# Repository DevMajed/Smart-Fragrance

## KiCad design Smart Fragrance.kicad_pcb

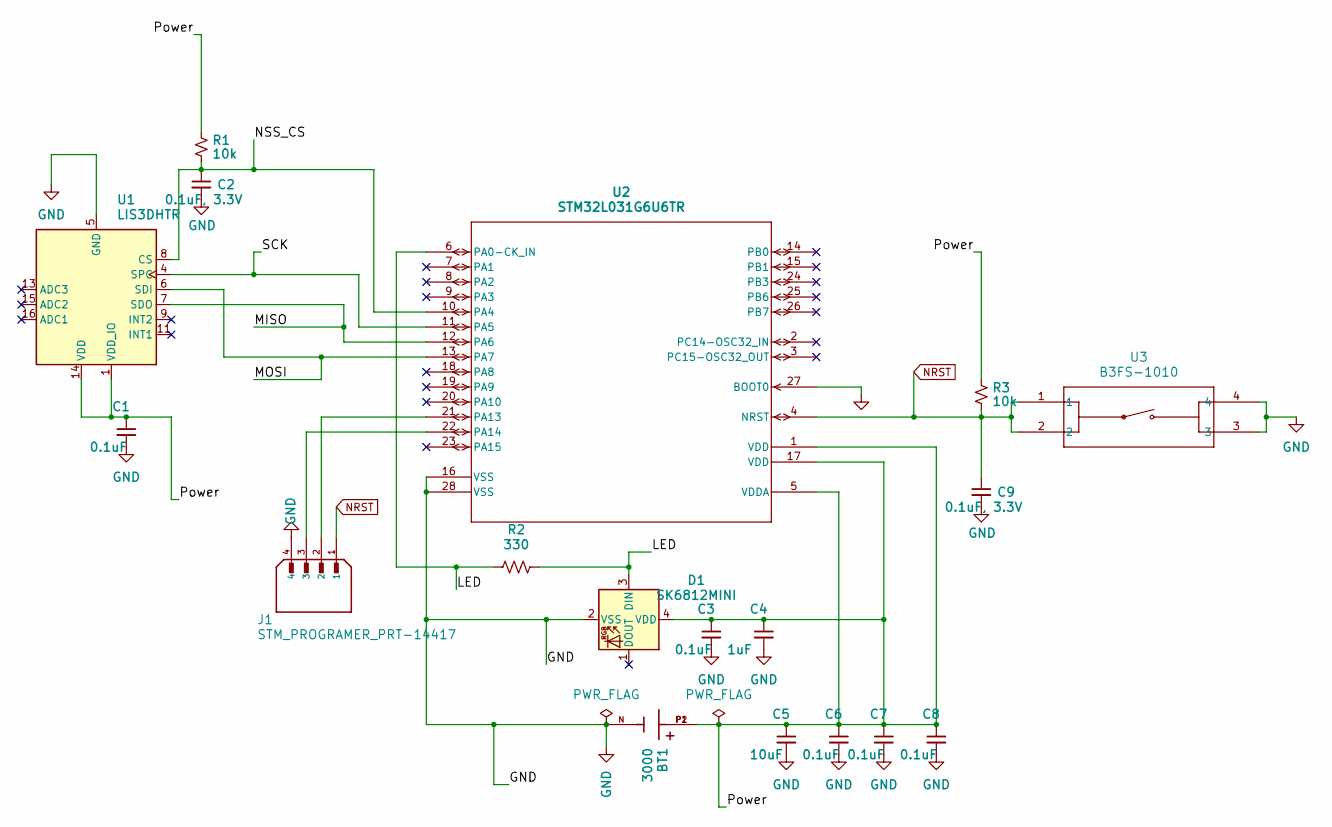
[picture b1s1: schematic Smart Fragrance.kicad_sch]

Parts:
BT1: 3000; BAT_3000; PARTREV M; Digikey 36-3000-ND
C1, C3, C6, C7, C8: 0.1uF; C_0603_1608Metric; Mfg part # CC0603KRX7R7BB104; Digikey 311-1088-1-ND
C2, C9: 0.1uF, 3.3V; C_0402_1005Metric; Mfg part # CC0402KRX7R8BB104; Digikey 311-2077-1-ND
C4: 1uF; C_0603_1608Metric; Mfg part # CC0603KRX5R8BB105; Digikey 311-1445-1-ND
C5: 10uF; C_0603_1608Metric; Mfg part # CC0603MRX5R6BB106; Digikey 311-1817-1-ND
D1: SK6812MINI; LED_SK6812MINI_PLCC4_3.5x3.5mm_P1.75mm; Mfg part # 2686; Digikey 1528-1541-ND
J1: STM_PROGRAMER_PRT-14417; SPARKFUN_PRT-14417; PARTREV NA; Digikey 1568-14417-ND
R1, R3: 10k; R_0402_1005Metric; Mfg part # RC0402JR-0710KL; Digikey 311-10KJRCT-ND
R2: 330; R_0402_1005Metric; Mfg part # RC0603JR-07330RL; Digikey 311-330GRCT-ND
U1: LIS3DHTR; LGA-16_3x3mm_P0.5mm_LayoutBorder3x5y; Mfg part # LIS3DHTR; Digikey 497-10613-2-ND
U2: STM32L031G6U6TR; UFQFPN28-4x4mm; Mfg part # STM32L031G6U6TR; Digikey 497-18805-2-ND
U3: B3FS-1010; B3FS-101_OMR; Mfg part # B3FS-1010; Digikey SW1141-ND

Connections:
/LED: D1.3 (DIN), R2.1, R2.2, U2.6 (PA0-CK_IN)
/MISO: U1.7 (SDO), U2.12 (PA6)
/MOSI: U1.6 (SDI), U2.13 (PA7)
/NSS_CS: C2.1, R1.2, U1.8 (CS), U2.10 (PA4)
/Power: BT1.P1, BT1.P2, C1.1, C3.1, C4.1, C5.1, C6.1, C7.1, C8.1, D1.4 (VDD), R1.1, R3.1, U1.1 (VDD_IO), U1.14 (VDD), U2.1 (VDD), U2.5 (VDDA), U2.17 (VDD)
/SCK: U1.4 (SPC), U2.11 (PA5)
GND: BT1.N, C1.2, C2.2, C3.2, C4.2, C5.2, C6.2, C7.2, C8.2, C9.2, D1.2 (VSS), J1.4, U1.5 (GND), U1.10 (GND), U1.12 (GND), U2.16 (VSS), U2.27 (BOOT0), U2.28 (VSS), U3.3, U3.4
NRST: C9.1, J1.1, R3.2, U2.4 (NRST), U3.1, U3.2
unnamed: J1.2, U2.21 (PA13)
unnamed: J1.3, U2.22 (PA14)

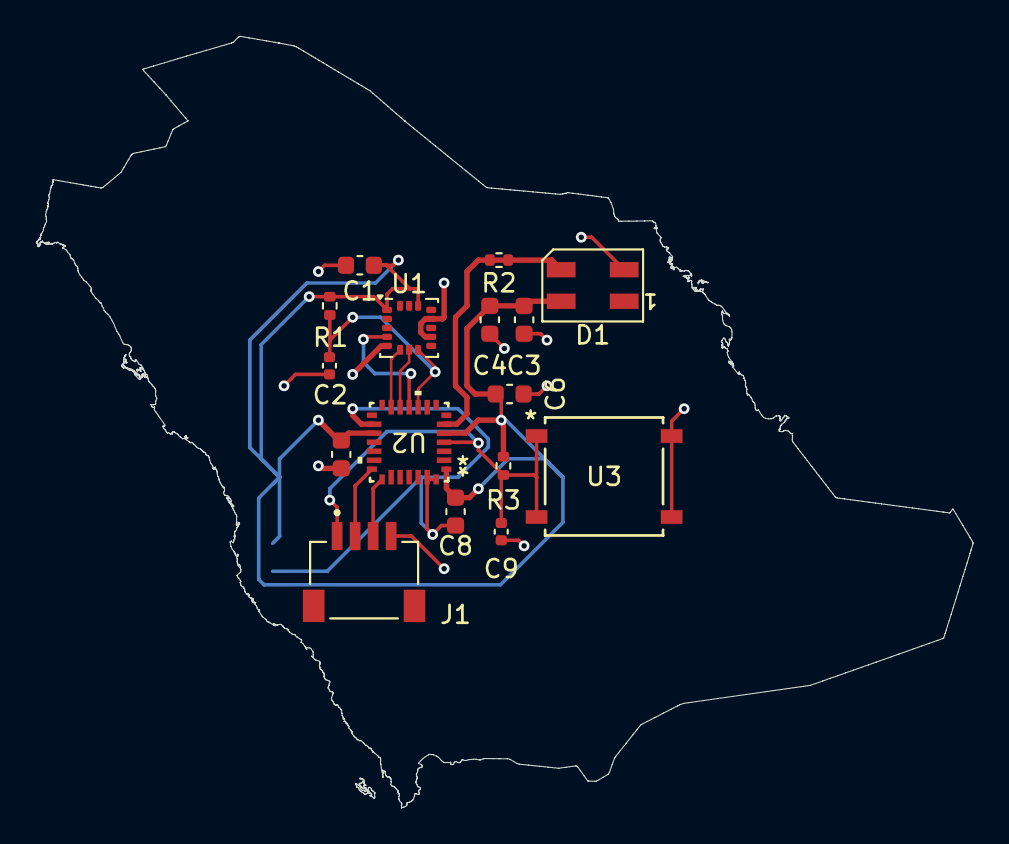
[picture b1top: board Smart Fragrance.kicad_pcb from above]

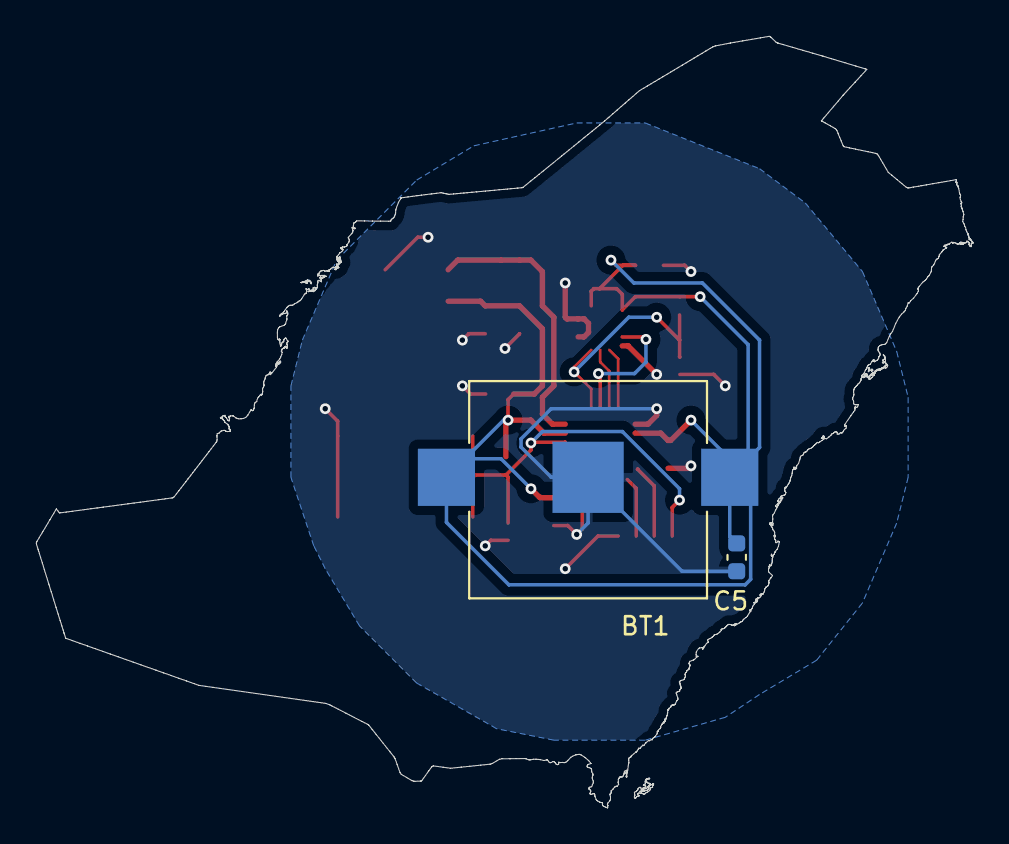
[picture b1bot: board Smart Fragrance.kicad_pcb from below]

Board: 2 copper layers, 52.0 x 42.9 mm, 18 parts (2 on the bottom side), 10 nets.

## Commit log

2025-07-13 layout is done
